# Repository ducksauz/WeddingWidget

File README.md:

WeddingWidget
=============

A blinkenlights toy for m33p and den's wedding favor.

So, my friends m33p and dennis are having an 8-bit themed wedding. They're both geeks and gamers, so it makes total sense and is awesome. They asked me for some help coming up with a wedding favor that has some sort of blinkenlights to it. I was given a budget of $5-10 per unit, the lower the better. A month or so beforehand I had seen [TinyMatrix](https://sites.google.com/site/tinymatrix/) by TigerUp pop up in my feeds and figured that had the right balance of blinking and cost. They loved it.

Since we need 50-75 of these, doing it deadbug style like TigerUp did was out of the question. PCBs and surface mount is the way to go on this one. I decided that the ATtiny88 was going to be our best value for the microconroller. So, I ordered some parts so I could start prototyping and got to work on the PCB design.

Once the breadboard prototype was built, I went to work on the minimal porting required to make the ATtiny2313 code run on an ATtiny88.

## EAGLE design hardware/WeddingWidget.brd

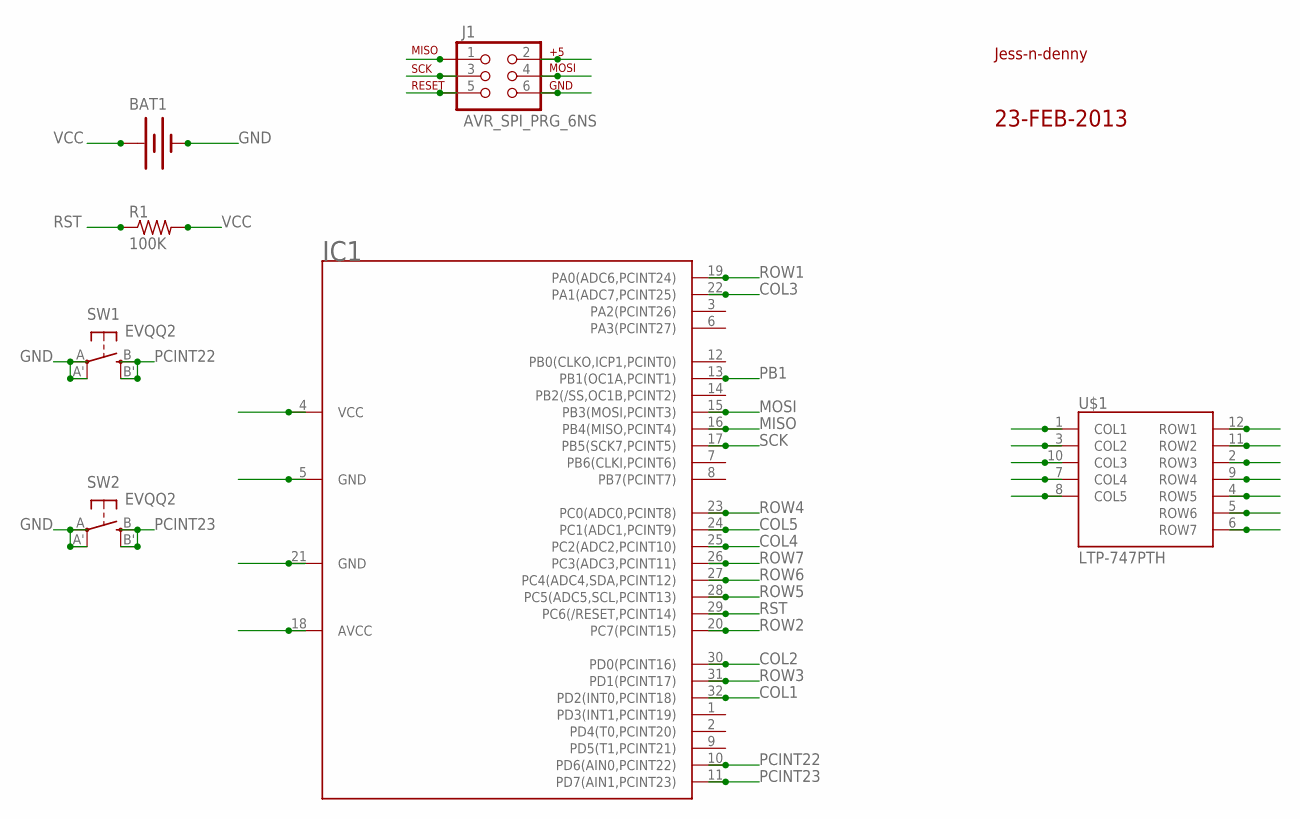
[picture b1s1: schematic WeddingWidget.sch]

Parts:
BAT1: BATTERY12MM; BATTCON_12MM
IC1: ATTINY88; TQFP32-08
J1: AVR_SPI_PRG_6NS; 2X3-NS
R1: 100K; M0805
SW1, SW2: EVQQ2; EVQ-Q2
U$1: LTP-747PTH; LTP-747
U$2: JESS-N-DENNY
U$3: 23FEB2013

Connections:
COL1: IC1.32 (PD2(INT0,PCINT18)), U$1.1 (COL1)
COL2: IC1.30 (PD0(PCINT16)), U$1.3 (COL2)
COL3: IC1.22 (PA1(ADC7,PCINT25)), U$1.10 (COL3)
COL4: IC1.25 (PC2(ADC2,PCINT10)), U$1.7 (COL4)
COL5: IC1.24 (PC1(ADC1,PCINT9)), U$1.8 (COL5)
GND: BAT1.GND (-), IC1.5 (GND), IC1.21 (GND), J1.6, SW1.A, SW1.A' (P1), SW2.A, SW2.A' (P1)
MISO: IC1.16 (PB4(MISO,PCINT4)), J1.1
MOSI: IC1.15 (PB3(MOSI,PCINT3)), J1.4
PB1: IC1.13 (PB1(OC1A,PCINT1))
PCINT22: IC1.10 (PD6(AIN0,PCINT22)), SW1.B (S), SW1.B' (S1)
PCINT23: IC1.11 (PD7(AIN1,PCINT23)), SW2.B (S), SW2.B' (S1)
ROW1: IC1.19 (PA0(ADC6,PCINT24)), U$1.12 (ROW1)
ROW2: IC1.20 (PC7(PCINT15)), U$1.11 (ROW2)
ROW3: IC1.31 (PD1(PCINT17)), U$1.2 (ROW3)
ROW4: IC1.23 (PC0(ADC0,PCINT8)), U$1.9 (ROW4)
ROW5: IC1.28 (PC5(ADC5,SCL,PCINT13)), U$1.4 (ROW5)
ROW6: IC1.27 (PC4(ADC4,SDA,PCINT12)), U$1.5 (ROW6)
ROW7: IC1.26 (PC3(ADC3,PCINT11)), U$1.6 (ROW7)
RST: IC1.29 (PC6(/RESET,PCINT14)), J1.5, R1.1
SCK: IC1.17 (PB5(SCK7,PCINT5)), J1.3
VCC: BAT1.V+ (+), IC1.4 (VCC), IC1.18 (AVCC), J1.2, R1.2

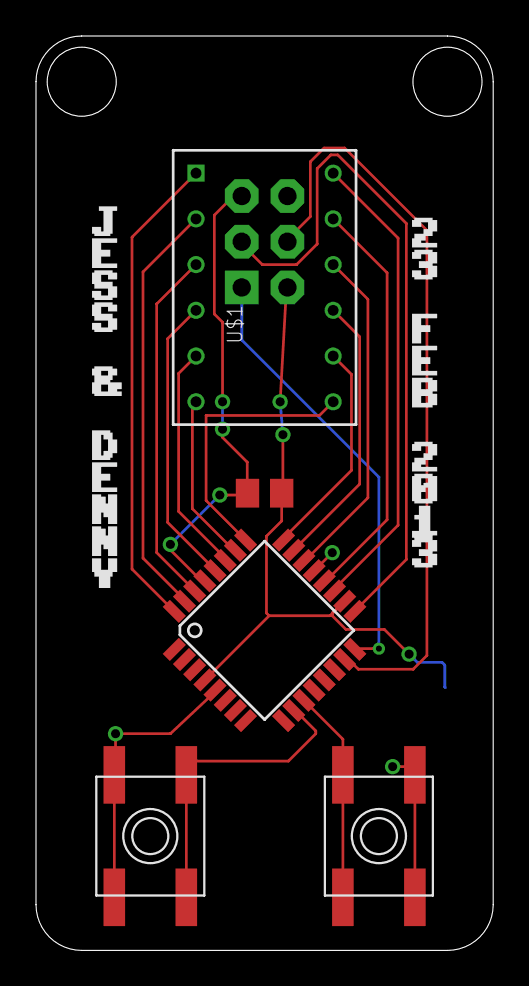
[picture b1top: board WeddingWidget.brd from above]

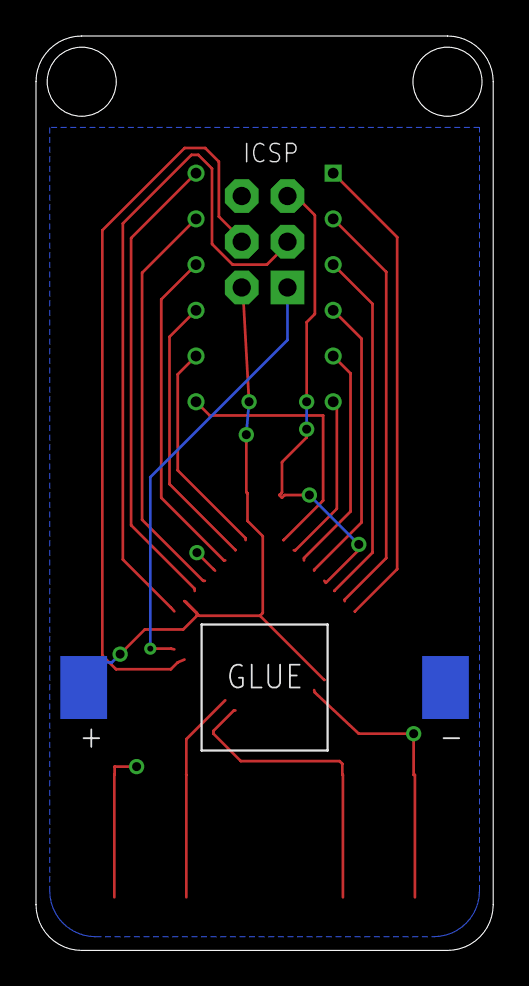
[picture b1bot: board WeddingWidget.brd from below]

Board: 2 copper layers, 25.4 x 50.8 mm, 9 parts (2 on the bottom side), 20 nets.

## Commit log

2012-11-17 Initial checkin of actual project files. Board design is 95% complete. Firmware is working with the attiny88 and this layout.
2012-11-17 ignoring elf and hex output
2012-11-17 README update
2012-11-17 updated copyright notice
2012-11-18 added battery holder and bottom ground plane
2012-11-18 Hand routed all traces. Ready for prototype boards to be produced.
2012-11-18 Dropped bitmapped text for prototype run.
2012-11-19 Fixed bitmap font text and added to board.
2012-11-19 added bitmap text to board
2012-11-20 Added alphabet to the symbolset
2012-12-09 Final design. Sent for manufacturing.
2012-12-09 extra art for production run
2012-12-09 minor change
2013-07-09 checking in Dennis's addition of the breakout game
